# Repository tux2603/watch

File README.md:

# Binary Watch

_revision 2.0_

A 12 hour wrist watch that displays the current time in BCD using LEDs. The watch is powered by a single CR2032 coin cell and uses an ATtiny402 microcontroller to keep track of time and drive the LEDs. The time can be viewed or set at any time by pressing the two buttons on the face of the watch.

PCB fabrication for this project was sponsered by [PCBWay](https://www.pcbway.com/), and I would like to thank them for their support! I was very happy with the quality of the PCBs they sent me, and their staff was very easy to work with.

_Fully assembled PCB, supplied by PCBWay and hand assembled by me. US penny for scale_

## Instructions

### Viewing the time

To view the time, simply press the `VIEW` button on the face of the watch. This will automatically wake the microcontroller and display the current time for 10 seconds. After 10 seconds, the LEDs will be turned off and the microcontroller will go back to sleep, conserving battery life.

### Setting the time

To set the time, first wake the watch from sleep by pressing the `VIEW` button. Once the watch is awake, press the `SET` button. The watch will now be in time setting mode, and the digit that is currently selected will flash once every two seconds. To change the value of the currently selected digit, press the `VIEW` button. Once the desired value is entered, press the `SET` button again to select the next digit and repeat until all digits are set. Once all digits are set, the watch will automatically return to view mode and go back to sleep after 10 seconds.

### Resetting the watch

To reset the watch, first wake the watch from sleep by pressing the `VIEW` button. Once the watch is awake, press and hold either button for at least three seconds. The watch will save the currently set time before resetting and will automatically return to view mode after the reset is complete.

## Design

Some trickery was needed to drive twelve LEDs and read two push buttons with the limited number of GPIO pins available. The LEDs are arranged in a [charlieplexing matrix](https://en.wikipedia.org/wiki/Charlieplexing), allowing all twelve LEDs to be controlled with just four tri-state GPIO pins. The push buttons are then read using a small resistor ladder with a single GPIO pin. Pressing the `VIEW` button will pull the voltage on the pin to `GND`, and pressing the `SET` button will pull the voltage on the pin to `0.5 * Vdd`. If no button is pressed, the voltage on the pin is pulled to `Vdd`. This way, only five GPIO pins are used and `PA0` is left to function solely as the UPDI pin, allowing for easy programming of the ATtiny402.

### Electronics BOM

| Description                | Count | Manufacturer Part Number | DigiKey Part Number  | Substitutions                                                                                |
| -------------------------- | ----- | ------------------------ | -------------------- | -------------------------------------------------------------------------------------------- |
| CR2032 coin cell holder    | 1     | BAT-HLD-001-TR           | BAT-HLD-001-TRCT-ND  | Substitutions are possible, but will require traces to be re-routed                          |
| Blue LED                   | 12    | IN-S63BT5B               | 1830-1068-1-ND       | Any other 0603 LED can be used, but if a different color is used the color will be different |
| 47Ω 1/8W Resistor          | 4     | ERJ-H3GJ470V             | 10-ERJ-H3GJ470VCT-ND | Any 0603, 47Ω resistor with a power rating of 1/8W or higher                                 |
| 4.7kΩ 1/8W Resistor        | 1     | ERJ-H3GJ472V             | 10-ERJ-H3GJ472VCT-ND | Any 0603, 4.7kΩ resistor with a power rating of 1/8W or higher                               |
| 10kΩ 1/8W Resistor         | 2     | ERJ-H3GJ103V             | 10-ERJ-H3GJ103VCT-ND | Any 0603, 4.7kΩ resistor with a power rating of 1/8W or higher                               |
| Momentary switch           | 2     | EVP-AA202K               | P13348SCT-ND         | Substitutions are possible, but will require traces to be re-routed                          |
| ATtiny 402 microcontroller | 1     | ATTINY402-SSNR           | ATTINY402-SSNRCT-ND  | Any ATtiny402. The ATtiny202 should also work, but has less flash and has not been tested.   |

### Mechanical BOM

| Description      | Count | Source                                   |
| ---------------- | ----- | ---------------------------------------- |
| Watch Body       | 1     | [CAD file](cad/watch-body.step)          |
| Watch Back       | 1     | [CAD file](cad/watch-back.step)          |
| PCB              | 1     | [Gerber files](pcb/gerbers.zip)          |
| CR2032 coin cell | 1     | Your favorite source for watch batteries |
| 18mm watch band  | 1     | Your favorite source for watch bands     |

## Assembly

### PCB

Unless you're lucky enough to have PCB fabrication facilities in house, you'll need to send the Gerber files to a third-party manufacturer for fabrication. I used DKRed for my initial prototypes, but after releasing v1 [PCBWay](https://www.pcbway.com/) reached out to me and offered to sponsor PCB fabrication for v2. Since I had selected tolerances to work with all of the major PCB fabrication services, I was more than happy to accept their offer. Having worked with both DKRed's ENIG finish and PCBWay's HASL finish, I would definietly have to say I preffered PCBWay's HASL for hand-soldering. The HASL finish made the soldering process a little bit easier, which when you're hand soldering small SMD components is always appreciated.

The components for the watch were picked to make hand soldering possible with a decent soldering iron and a steady hand, but it should also be possible to use a reflow oven or hot plate to solder the components on the face of the PCB. The battery holder will still likely need to be soldered by hand though, but it's nice and big so it shouldn't be too difficult. For hand soldering, I used the following procedure:

1.  Solder the LEDs and 47Ω resistors to the middle section of the PCB.

    - The resistors go in the spots with the two parallel silk screen lines (1, 3, 5, and 9 in Figure 1). These resistors aren't polarized, so they can be soldered in any orientation.
    - The LEDs go in the spots with the C-shaped silk screen lines around them (2, 4, 6, 7, 8, 10, 11, 12, 13, 14, 15, and 16 in Figure 1). The LEDs are polarized, so make sure to solder them in the correct orientation. If you use the LEDs specified in the BOM, the cathode will be marked with a tiny green dot. This green dot should be facing towards the C-shaped silk screen line. This orientation is also shown in Figure 1.

    _Figure 1_: LED and resistor placement

2.  Verify that the resistors and LEDs were placed correctly

    - Apply the positive and negative connections to a 3.3V source to the pads shown in Figure 2 using the table below. If everything is soldered correctly, the corresponding

    | LED | Positive pad | Negative pad |
    | --- | ------------ | ------------ |
    | 2   | 1            | 2            |
    | 4   | 1            | 3            |
    | 6   | 3            | 1            |
    | 7   | 2            | 1            |
    | 8   | 3            | 2            |
    | 10  | 4            | 1            |
    | 11  | 1            | 4            |
    | 12  | 2            | 3            |
    | 13  | 4            | 2            |
    | 14  | 2            | 4            |
    | 15  | 4            | 3            |
    | 16  | 3            | 4            |

    _Figure 2_: LED test pads

3.  Solder the 4.7kΩ an 10kΩ resistors to the PCB

    - The 4.7kΩ resistor and two 10kΩ resistors go in the remaining spots with the two parallel silk screen lines (1, 2, and 3 in Figure 3). These resistors aren't polarized, so they can be soldered in any orientation.
      - The 4.7kΩ resistor goes in the spot with the two parallel silk screen lines in the upper-left corner of the PCB (1 in Figure 3)
      - The two 10kΩ resistors go in the spots with the two parallel silk screen lines in bottom center of the PCB (2 and 3 in Figure 3)

    _Figure 3_: Remaining resistor placement

4.  Solder the buttons to the PCB

    - The buttons go above the silk screen labels reading `SW1` and `SW2`. The buttons aren't polarized, so they can be soldered in either direction

5.  Solder the ATtiny402 to the PCB

    - The ATtiny402 goes in the remaining spot on the front of the PCB with the small dimple or notch in the chip facing the center of the PCB

6.  Solder the battery holder to the PCB

    - Flip the PCB over and solder the battery holder to the four pads on the back

### Flashing

Three solder pads, labeled VCC, GND, and UPDI, are supplied on the watch face to allow for simple programming of the ATtiny using a UPDI programmer. Any UPDI programmer should work, but I used an Arduino Uno running [jtag2updi](https://github.com/ElTangas/jtag2updi/). The 4.7k series resistor required for flashing is already included on the PCB, so no external resistor is necessary.

1. Connect the VCC, GND, and UPDI solder pads to the corresponding pins using jumper wires. These jumper wires can be soldered or clipped on, it doesn't really matter. Note that the pads and traces are very small and fragile, so be careful not to put too much stress on them or they could rip off of the PCB.

   - The VCC pad should be connected to the 5V pin on the Arduino
   - The GND pad should be connected to the GND pin on the Arduino
   - The UPDI pad should be connected to the D6 on the Arduino

2. Hook the Arduino up to your PC and note what port it is connected to (eg, COM3, /dev/ttyACM0, /dev/ttyUSB0, etc). Set the `PORT` variable on line four of the [Makefile](Makefile) to this value, replacing the default value of `/dev/ttyACM0`

3. Run `make flash` to flash the watch. Alternatively, you can manually run the command `avrdude -c jtag2updi -P <YOUR_PORT> -p attiny402 -U flash:w:bin/main.hex -U eeprom:w:bin/eeprom.hex` to flash the watch.

4. The watch should automatically enter calibration mode after flashing. If you don't want to calibrate the watch right now, just hold down the `VIEW` button for at least three seconds to reset the watch.

### Calibration

After flashing the firmware, the watch will automatically enter one-time calibration mode. In this mode the watch will generate a square wave on the `CAL` solder pad, which can be measured using an oscilloscope. The period of this waveform should be as close to 468.75ms as possible, but it will initially be a good deal off from this value. To calibrate the watch, follow these steps:

1. Connect the `CAL` solder pad to the positive terminal of an oscilloscope probe using a jumper wire. Connect the negative terminal of the probe to the `GND` solder pad.
2. Measure the period of the generated square wave and compare it to the desired value of 468.75ms.
   - If the measured period is to high, press the `VIEW` button to decrease the period.
   - If the measured period is to low, press the `SET` button to increase the period.
3. Repeat step 2 thirteen times. After the last repetition, the watch will automatically save the calibration value and restart into standard operation mode.

To prevent accidental re-calibration, the watch will only enter calibration mode immediately after flashing by default. If you want to enable entering calibration mode without flashing the watch, write the value `0x01` to EEPROM address `0x05`. This will allow the watch to enter calibration mode by holding down the `SET` button for at least three seconds. To disable this feature again, write the value `0x00` to EEPROM address `0x05`.

## Customization

The functionality of the watch can be customized by modifying, compiling, and flashing the [source code](src/main.c). For simple changes, the following configuration options can be modified in the [config.h](src/config.h) file:

| Option             | Description                                                                                                      | Default Value | Recommended Range | Units         |
| ------------------ | ---------------------------------------------------------------------------------------------------------------- | ------------- | ----------------- | ------------- |
| `BLINK_FREQUENCY`  | The frequency at which the currently selected digit will blink while in time setting mode                        | 1             | 0.25 - 2          | Hz            |
| `DEBOUNCE_COUNT`   | The number of consecutive update cycles that a button state must be stable before it is considered to be pressed | 50            | 5 - 500           | update cycles |
| `RESET_HOLD_TIME`  | The number of seconds that a button must be held before the watch is reset                                       | 3             | 1 - 10            | s             |
| `SLEEP_TIMEOUT`    | The number of seconds that the watch will remain awake before automatically going back to sleep                  | 10            | 1 - 60            | s             |
| `UPDATE_FREQUENCY` | The frequency at which the LED matrix is updated and input is read from the buttons.                             | 480           | 96 - 5000         | Hz            |

To compile the code, the avr-gcc tool chain will need to be installed with support for the ATtiny402

## License

This work is licensed under a [Creative Commons Attribution-NonCommercial 4.0 International License](https://creativecommons.org/licenses/by-nc/4.0). You are free to share, use, and modify this work for any non-commercial reasons as long as you give appropriate credit. The author grants permission for PCB and CAD design files to be sent to third-party manufacturers for fabrication as long as these fabricated parts or assemblies containing these fabricated parts are not later resold for profit.

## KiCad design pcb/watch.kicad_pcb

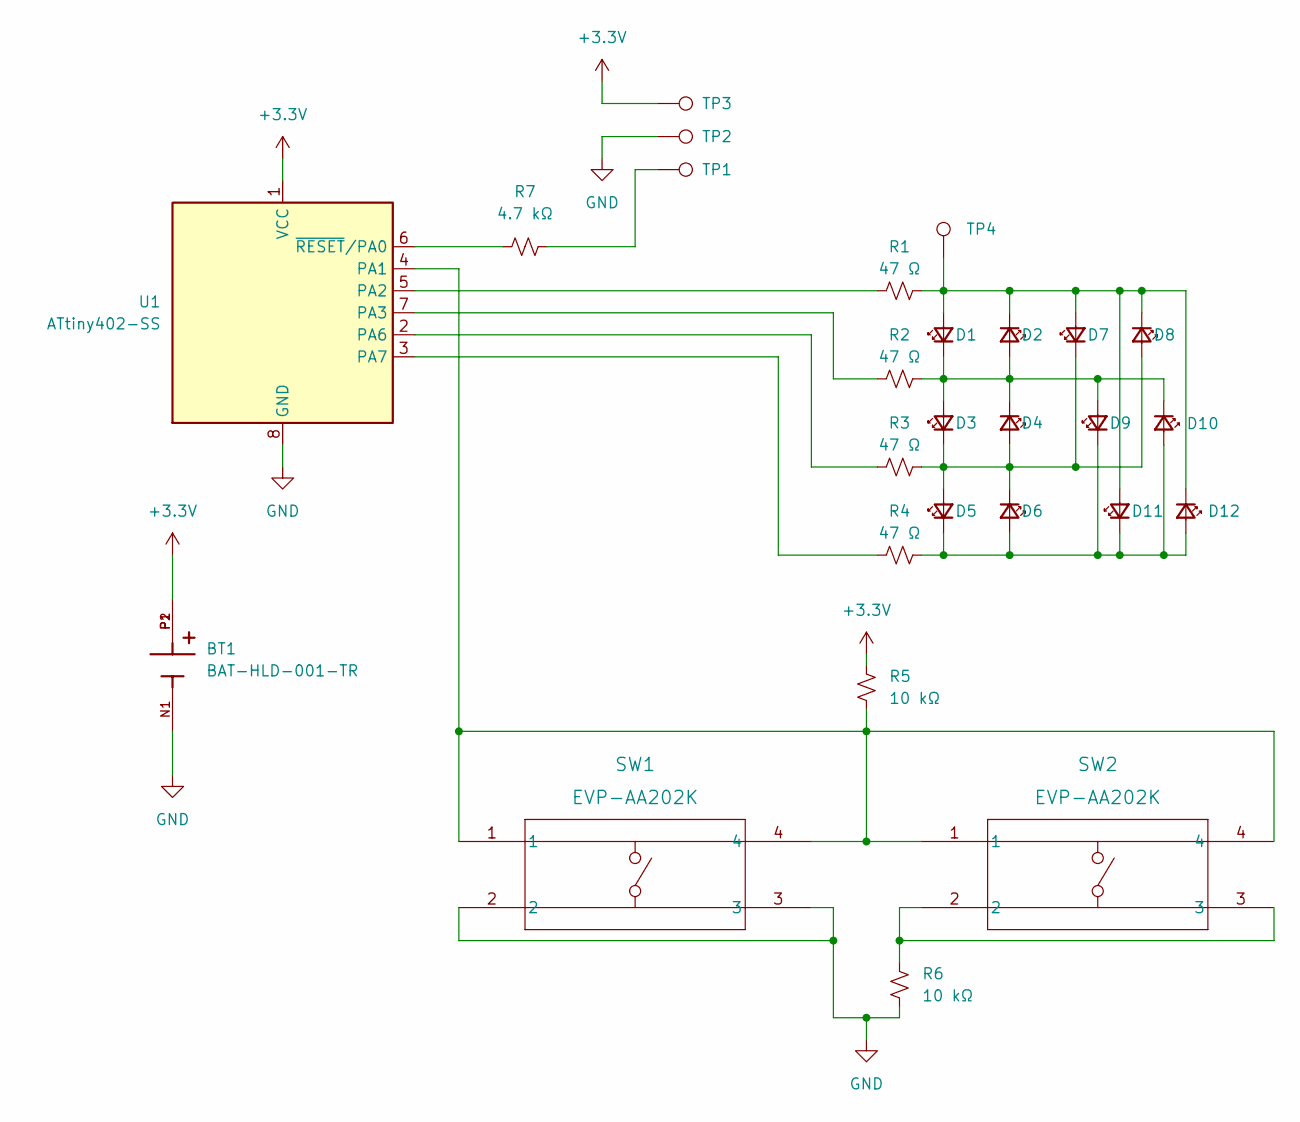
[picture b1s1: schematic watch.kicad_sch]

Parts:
BT1: BAT-HLD-001-TR; BAT_BAT-HLD-001-TR; PARTREV B
D1, D2, D3, D4, D5, D6, D7, D8, D9, D10, D11, D12: LED_Small; LED_0603_1608Metric
R1, R2, R3, R4: 47 Ω; R_0603_1608Metric
R5, R6: 10 kΩ; R_0603_1608Metric
R7: 4.7 kΩ; R_0603_1608Metric
SW1, SW2: EVP-AA202K; SW_EVP-AA102K_PAN
TP1, TP4: TestPoint; TestPoint_Pad_D1.0mm
TP2, TP3: TestPoint; TestPoint_Pad_1.0x1.0mm
U1: ATtiny402-SS; SOIC-8_3.9x4.9mm_P1.27mm

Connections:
+3.3V: BT1.P1, BT1.P2, R5.1, TP3.1, U1.1 (VCC)
GND: BT1.N1, R6.2, SW1.2, SW1.3, TP2.1, U1.8 (GND)
unnamed: D1.1 (K), D2.2 (A), D3.2 (A), D4.1 (K), D9.2 (A), D10.1 (K), R2.2
unnamed: D1.2 (A), D2.1 (K), D7.2 (A), D8.1 (K), D11.2 (A), D12.1 (K), R1.2, TP4.1
unnamed: D3.1 (K), D4.2 (A), D5.2 (A), D6.1 (K), D7.1 (K), D8.2 (A), R3.2
unnamed: D5.1 (K), D6.2 (A), D9.1 (K), D10.2 (A), D11.1 (K), D12.2 (A), R4.2
unnamed: R1.1, U1.5 (PA2)
unnamed: R2.1, U1.7 (PA3)
unnamed: R3.1, U1.2 (PA6)
unnamed: R4.1, U1.3 (PA7)
unnamed: R5.2, SW1.1, SW1.4, SW2.1, SW2.4, U1.4 (PA1)
unnamed: R6.1, SW2.2, SW2.3
unnamed: R7.1, U1.6 (~RESET/PA0)
unnamed: R7.2, TP1.1

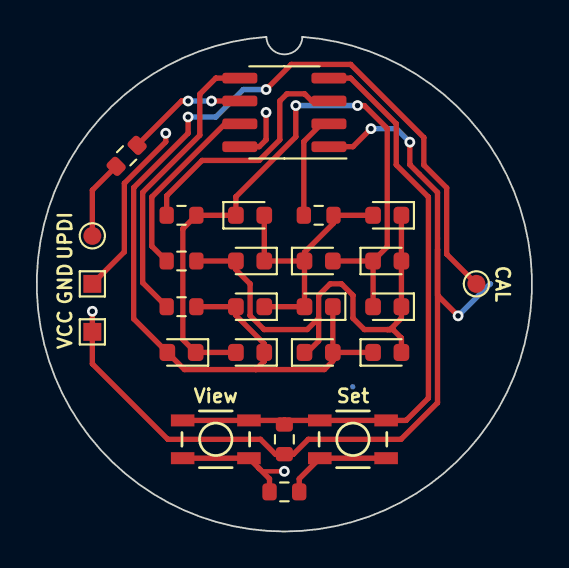
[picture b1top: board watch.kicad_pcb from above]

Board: 2 copper layers, 27.5 x 27.5 mm, 27 parts (1 on the bottom side), 14 nets.

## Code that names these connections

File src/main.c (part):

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
// ##### Pin IO masks and general constants #####

#define PA1 0x02
#define PA2 0x04
#define PA3 0x08
#define PA6 0x40
#define PA7 0x80

#define RESET_COUNT (RESET_HOLD_TIME * UPDATE_FREQUENCY)
#define SET_BTN_THRESHOLD 0xC0
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#if PCB_REVISION == 1

// Pins to write high for each of the time bits
#    define MM_L0_HIGH PA3
#    define MM_L1_HIGH PA7
#    define MM_L2_HIGH PA2
#    define MM_L3_HIGH PA2
#    define MM_H0_HIGH PA2
#    define MM_H1_HIGH PA6
#    define MM_H2_HIGH PA7
#    define HH_L0_HIGH PA7
#    define HH_L1_HIGH PA6
#    define HH_L2_HIGH PA3
#    define HH_L3_HIGH PA6
#    define HH_H0_HIGH PA3

// Pins to write low for each of the time bits
#    define MM_L0_LOW PA2
#    define MM_L1_LOW PA2
#    define MM_L2_LOW PA7
#    define MM_L3_LOW PA6
#    define MM_H0_LOW PA3
#    define MM_H1_LOW PA3
#    define MM_H2_LOW PA6
#    define HH_L0_LOW PA3
#    define HH_L1_LOW PA2
#    define HH_L2_LOW PA6
#    define HH_L3_LOW PA7
#    define HH_H0_LOW PA7

#elif PCB_REVISION == 2

// Pins to write high for each of the time bits
#    define MM_L0_HIGH PA3
#    define MM_L1_HIGH PA7
#    define MM_L2_HIGH PA3
#    define MM_L3_HIGH PA6
#    define MM_H0_HIGH PA2
#    define MM_H1_HIGH PA6
#    define MM_H2_HIGH PA7
#    define HH_L0_HIGH PA7
#    define HH_L1_HIGH PA2
#    define HH_L2_HIGH PA3
#    define HH_L3_HIGH PA6
#    define HH_H0_HIGH PA2

// Pins to write low for each of the time bits
#    define MM_L0_LOW PA2
#    define MM_L1_LOW PA3
#    define MM_L2_LOW PA7
#    define MM_L3_LOW PA3
#    define MM_H0_LOW PA3
#    define MM_H1_LOW PA2
#    define MM_H2_LOW PA6
#    define HH_L0_LOW PA2
#    define HH_L1_LOW PA6
#    define HH_L2_LOW PA6
#    define HH_L3_LOW PA7
#    define HH_H0_LOW PA7

#endif

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


const uint8_t led_high_pins[4] = {PA2, PA3, PA6, PA7};

const uint8_t led_low_pins[4][3] = {
    {PA3, PA6, PA7},
    {PA2, PA6, PA7},
    {PA2, PA3, PA7},
    {PA2, PA3, PA6}};


#if PCB_REVISION == 1
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    //  - TCB overflow will trigger the LEDs to update
    //  - ADC conversion will trigger the FSM to update
    //  - ADC window will reset the TCA CNT register to 0
    //  - A low level on PA1 will trigger the device to wake up
    CCP = CCP_IOREG_gc;                 // Allow access to protected registers
    CPUINT.CTRLA |= CPUINT_LVL0RR_bm;   // Enable round-robin scheduling
    CPUINT.LVL1VEC = TCA0_OVF_vect_num; // Set the TCA overflow interrupt to priority level 1
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    ADC0.CTRLC |= ADC_REFSEL0_bm | ADC_PRESC_DIV8_gc; // Set the ADC to use Vdd as reference and set the ADC clock prescaler to CLK_PER/8, or 1MHz/8 = 125kHz
    ADC0.CTRLD |= ADC_INITDLY_DLY32_gc;               // Set the ADC sampling delay to 32 CLK_ADC cycles after enabling
    ADC0.CTRLE |= ADC_WINCM_BELOW_gc;                 // Set the ADC window mode to below
    ADC0.MUXPOS |= ADC_MUXPOS_AIN1_gc;                // Set the ADC input to PA1
    ADC0.EVCTRL |= ADC_STARTEI_bm;                    // Set the ADC to be triggered by the event system
    ADC0.WINLT = SET_BTN_THRESHOLD;                   // Set the ADC window comparator low threshold to ~0.75*Vdd
    ADC0.INTCTRL |= ADC_RESRDY_bm | ADC_WCMP_bm;      // Enable the ADC result ready and window comparator interrupt
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

    // ##### Configure PORTA #####
    // The default state of all pins will be inputs with pull-ups disabled. PA2, PA3, PA6, and PA7
    //  are used to charlieplex a matrix of 12 LEDs, and will be toggled to digital outputs
    //  as appropriate in a timed interrupt.:hat is triggered on a low level.
    PORTA.DIRCLR = PA2 | PA3 | PA6 | PA7; // Set LED pins to inputs
    PORTA.DIRCLR = PA1;                   // Set the switch pin to an input
}

#ifdef ENABLE_CALIBRATION_MODE
void init_cal() {

    // To calibrate the watch, a square wave with a period of ~468.75ms will be generated
    //  on PA2. This square wave will be measured with an external oscilloscope, and the
    //  RTC period register will be adjusted through SAR until the measured period is within
    //  10us of 468.75ms. Once the period is within tolerance, the value of the RTC period
    //  register will be saved to EEPROM and the device will be reset into standard operating
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

    // ##### Configure RTC #####
    // The RTC will be used to trigger an interrupt to generate a square wave on PA2 with a
    //  period of ~1.875 seconds. The actual period of the square wave will be measured with
    //  an external oscilloscope, and the RTC period will be adjusted through SAR until the
    //  period is 1.875 seconds, +/- 10us.
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    ADC0.CTRLC |= ADC_REFSEL0_bm;       // Set the ADC to use Vdd as reference
    ADC0.CTRLC |= ADC_PRESC_DIV8_gc;    // Set the ADC clock prescaler to CLK_PER/8, or 1MHz/8 = 125kHz
    ADC0.CTRLD |= ADC_INITDLY_DLY32_gc; // Set the ADC sampling delay to 32 CLK_ADC cycles after enabling
    ADC0.MUXPOS |= ADC_MUXPOS_AIN1_gc;  // Set the ADC input to PA1
    ADC0.EVCTRL |= ADC_STARTEI_bm;      // Set the ADC to be triggered by the event system
    ADC0.INTCTRL |= ADC_RESRDY_bm;      // Enable the ADC result ready interrupt
    ADC0.CTRLA |= ADC_ENABLE_bm;        // Enable the ADC


    // ##### Configure PORTA #####
    // PA1 will be used as an analog input, PA2 will be used as a digital output
    //  for the square wave, and PA3 will be a digital output with a constant value
    //  of Vdd so that the bottom right LED will light up when the square wave is active
    PORTA.DIRCLR = PA1; // Set the switch pin to an input
    PORTA.DIRSET = PA2; // Set the square wave pin to an output
    PORTA.OUTCLR = PA2; // Set the square wave pin to low
    PORTA.DIRSET = PA3; // Set the constant Vdd pin to an output
    PORTA.OUTSET = PA3; // Set the constant Vdd pin to high
}
#endif

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    TCA0.SINGLE.INTFLAGS = TCA_SINGLE_OVF_bm;                 // Clear the interrupt flag
    if (current_state != FSM_DISPLAY) return;                 // Only enter sleep if not on one of the set modes
    current_state == FSM_BLANK;                               // Set the state to blank
    PORTA.OUTCLR = PA2 | PA3 | PA6 | PA7;                     // Set all four LED pins to low
    PORTA.DIRCLR = PA2 | PA3 | PA6 | PA7;                     // Set all four LED pins to be inputs
    TCA0.SINGLE.CTRLA &= ~TCA_SINGLE_ENABLE_bm;               // Disable TCA0
    TCB0.CTRLA &= ~TCB_ENABLE_bm;                             // Disable TCB0
    ADC0.CTRLA &= ~ADC_ENABLE_bm;                             // Disable ADC0
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    TCB0.INTFLAGS = TCB_CAPT_bm;

    // Set all four LED pins to low and to be inputs
    PORTA.OUTCLR = PA2 | PA3 | PA6 | PA7;
    PORTA.DIRCLR = PA2 | PA3 | PA6 | PA7;

    // Only power LEDs if the current FSM state isn't FSM_BLANK
    if (current_state == FSM_BLANK) return;
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#ifdef ENABLE_CALIBRATION_MODE
    if (active_mode == MODE_CAL) {
        // Toggle the square wave pin
        PORTA.OUTTGL = PA2;
    } else
#endif

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
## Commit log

2023-05-24 Add initial PCB files
2023-05-24 Add CC BY-NC license
2023-05-25 Initial peripheral config and makefile
2023-05-25 Remember to enable ADC and better defines
2023-05-25 Get the interrupt vector names right
2023-05-26 Add interrupts
2023-05-26 Reconfigure pcb constraints for DKRed
2023-06-01 Add alignment notch to PCB
2023-06-01 Add step files for watch case
2023-06-01 Add 3D component models Also fix silk screen and add rendered image of PCB
2023-06-01 Move cad files to a more appropriate folder name
2023-06-01 Simplify make file
2023-06-01 Move simple config options to a header file
2023-06-01 Initial readme
2023-06-01 Add prusa slicer project file to gitignore
2023-06-01 Update gerber files
2023-06-01 Add 3mf versions of designs to gitignore
2023-06-08 Fix bugs, working release Reset currently doesn't work, but we didn't need that anyway
2023-06-10 Increase LED brightness by ~3x
2023-06-10 Fix view and set silkscreen labels
2023-06-11 Make the PCB more aesthetically pleasing
2023-06-12 Add simple clock calibration
2023-06-12 Add 'flash' target to make file
2023-06-12 Nudge silkscreen labels off of the traces
2023-06-13 EEPROM flag to prevent accidental recalibration
2023-06-13 Use a CR2032 instead of a CR1216
2023-06-13 Add alignment dots to PCB image
2023-06-16 Modify PCB to work with more fabrication services Also rotate the alignment pin
2023-06-24 Fix wrong LEDs blinking for v1 PCB
2023-06-24 Minor PCB tweaks
2023-07-02 Code size optimizations
2023-07-02 Update readme to include size optimization option
2023-08-05 Fix the minutes digit displaying incorrect values
2023-08-29 Add image of assembled PCB
2023-08-29 Add thanks for PCBWay sponsorshi[
